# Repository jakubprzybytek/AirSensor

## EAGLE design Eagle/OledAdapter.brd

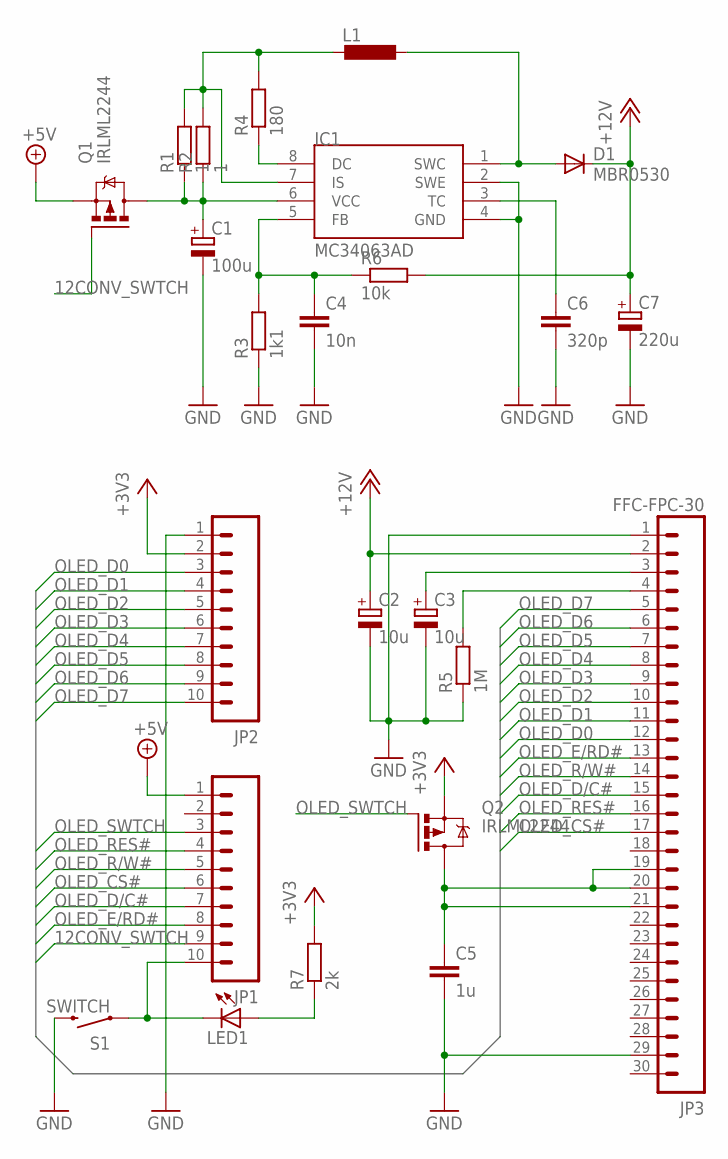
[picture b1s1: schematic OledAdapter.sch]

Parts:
C1: 100u; UD-6,3X7,7_NICHICON
C2, C3: 10u; UD-4X5,8_NICHICON
C4: 10n; C0805
C5: 1u; C1206
C6: 320p; C0805
C7: 220u; UD-6,3X7,7_NICHICON
D1: MBR0530; SOD123
IC1: MC34063AD; SOIC8
JP1, JP2: M10SILK_FEMALE_PTH; 1X10
JP3: FFC-FPC-30; FFC-FPC-30V
L1: L-EUL8530M; L8530M
LED1: LEDSML1206; SML1206
Q1, Q2: IRLML2244; MICRO3
R1, R2: 1; R0805
R3: 1k1; R0805
R4: 180; R0805
R5: 1M; M1206
R6: 10k; R0805
R7: 2k; R0805
S1: SWITCH; TACTILE-SWITCH-1101NE

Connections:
12CONV_SWTCH: JP1.9, Q1.1 (G)
+3V3: JP2.2, Q2.2 (S), R7.2
+5V: JP1.1, Q1.2 (S)
+12V: C2.+, C7.+, D1.C, JP3.2, R6.2
GND: C1.-, C2.-, C3.-, C4.2, C5.2, C6.2, C7.-, IC1.2 (SWE), IC1.4 (GND), JP2.1, JP3.1, JP3.29, R3.1, R5.1, S1.2
unnamed: JP1.10, LED1.C, S1.1
unnamed: LED1.A, R7.1
unnamed: C1.+, IC1.6 (VCC), Q1.3 (D), R1.1, R2.1
unnamed: C3.+, JP3.3
unnamed: C5.1, JP3.19, JP3.20, JP3.21, Q2.3 (D)
unnamed: IC1.7 (IS), L1.2, R1.2, R2.2, R4.2
unnamed: JP3.4, R5.2
unnamed: IC1.8 (DC), R4.1
unnamed: D1.A, IC1.1 (SWC), L1.1
unnamed: C6.1, IC1.3 (TC)
unnamed: C4.1, IC1.5 (FB), R3.2, R6.1
OLED_CS#: JP1.6, JP3.17
OLED_D0: JP2.3, JP3.12
OLED_D1: JP2.4, JP3.11
OLED_D2: JP2.5, JP3.10
OLED_D3: JP2.6, JP3.9
OLED_D4: JP2.7, JP3.8
OLED_D5: JP2.8, JP3.7
OLED_D6: JP2.9, JP3.6
OLED_D7: JP2.10, JP3.5
OLED_D/C#: JP1.7, JP3.15
OLED_E/RD#: JP1.8, JP3.13
OLED_R/W#: JP1.5, JP3.14
OLED_RES#: JP1.4, JP3.16
OLED_SWTCH: JP1.3, Q2.1 (G)

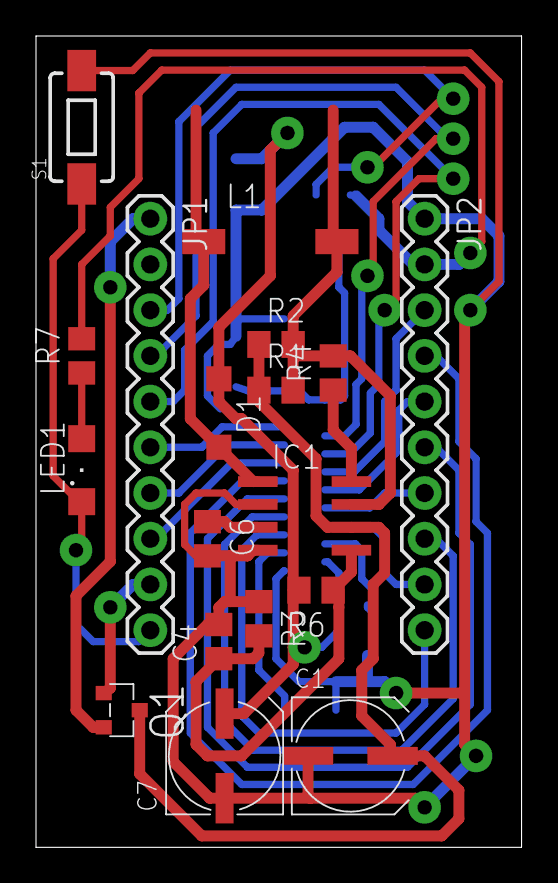
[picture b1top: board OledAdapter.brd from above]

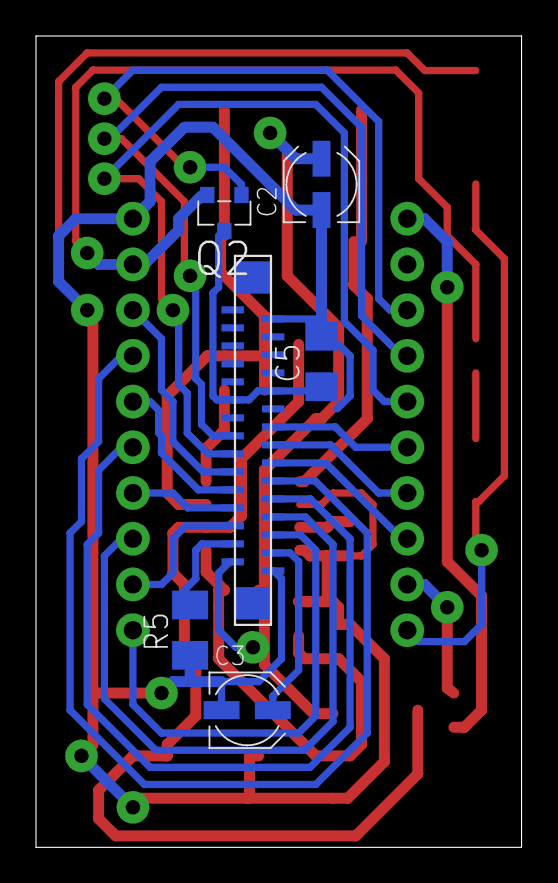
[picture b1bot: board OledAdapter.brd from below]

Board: 2 copper layers, 27.0 x 45.1 mm, 24 parts (6 on the bottom side), 30 nets.

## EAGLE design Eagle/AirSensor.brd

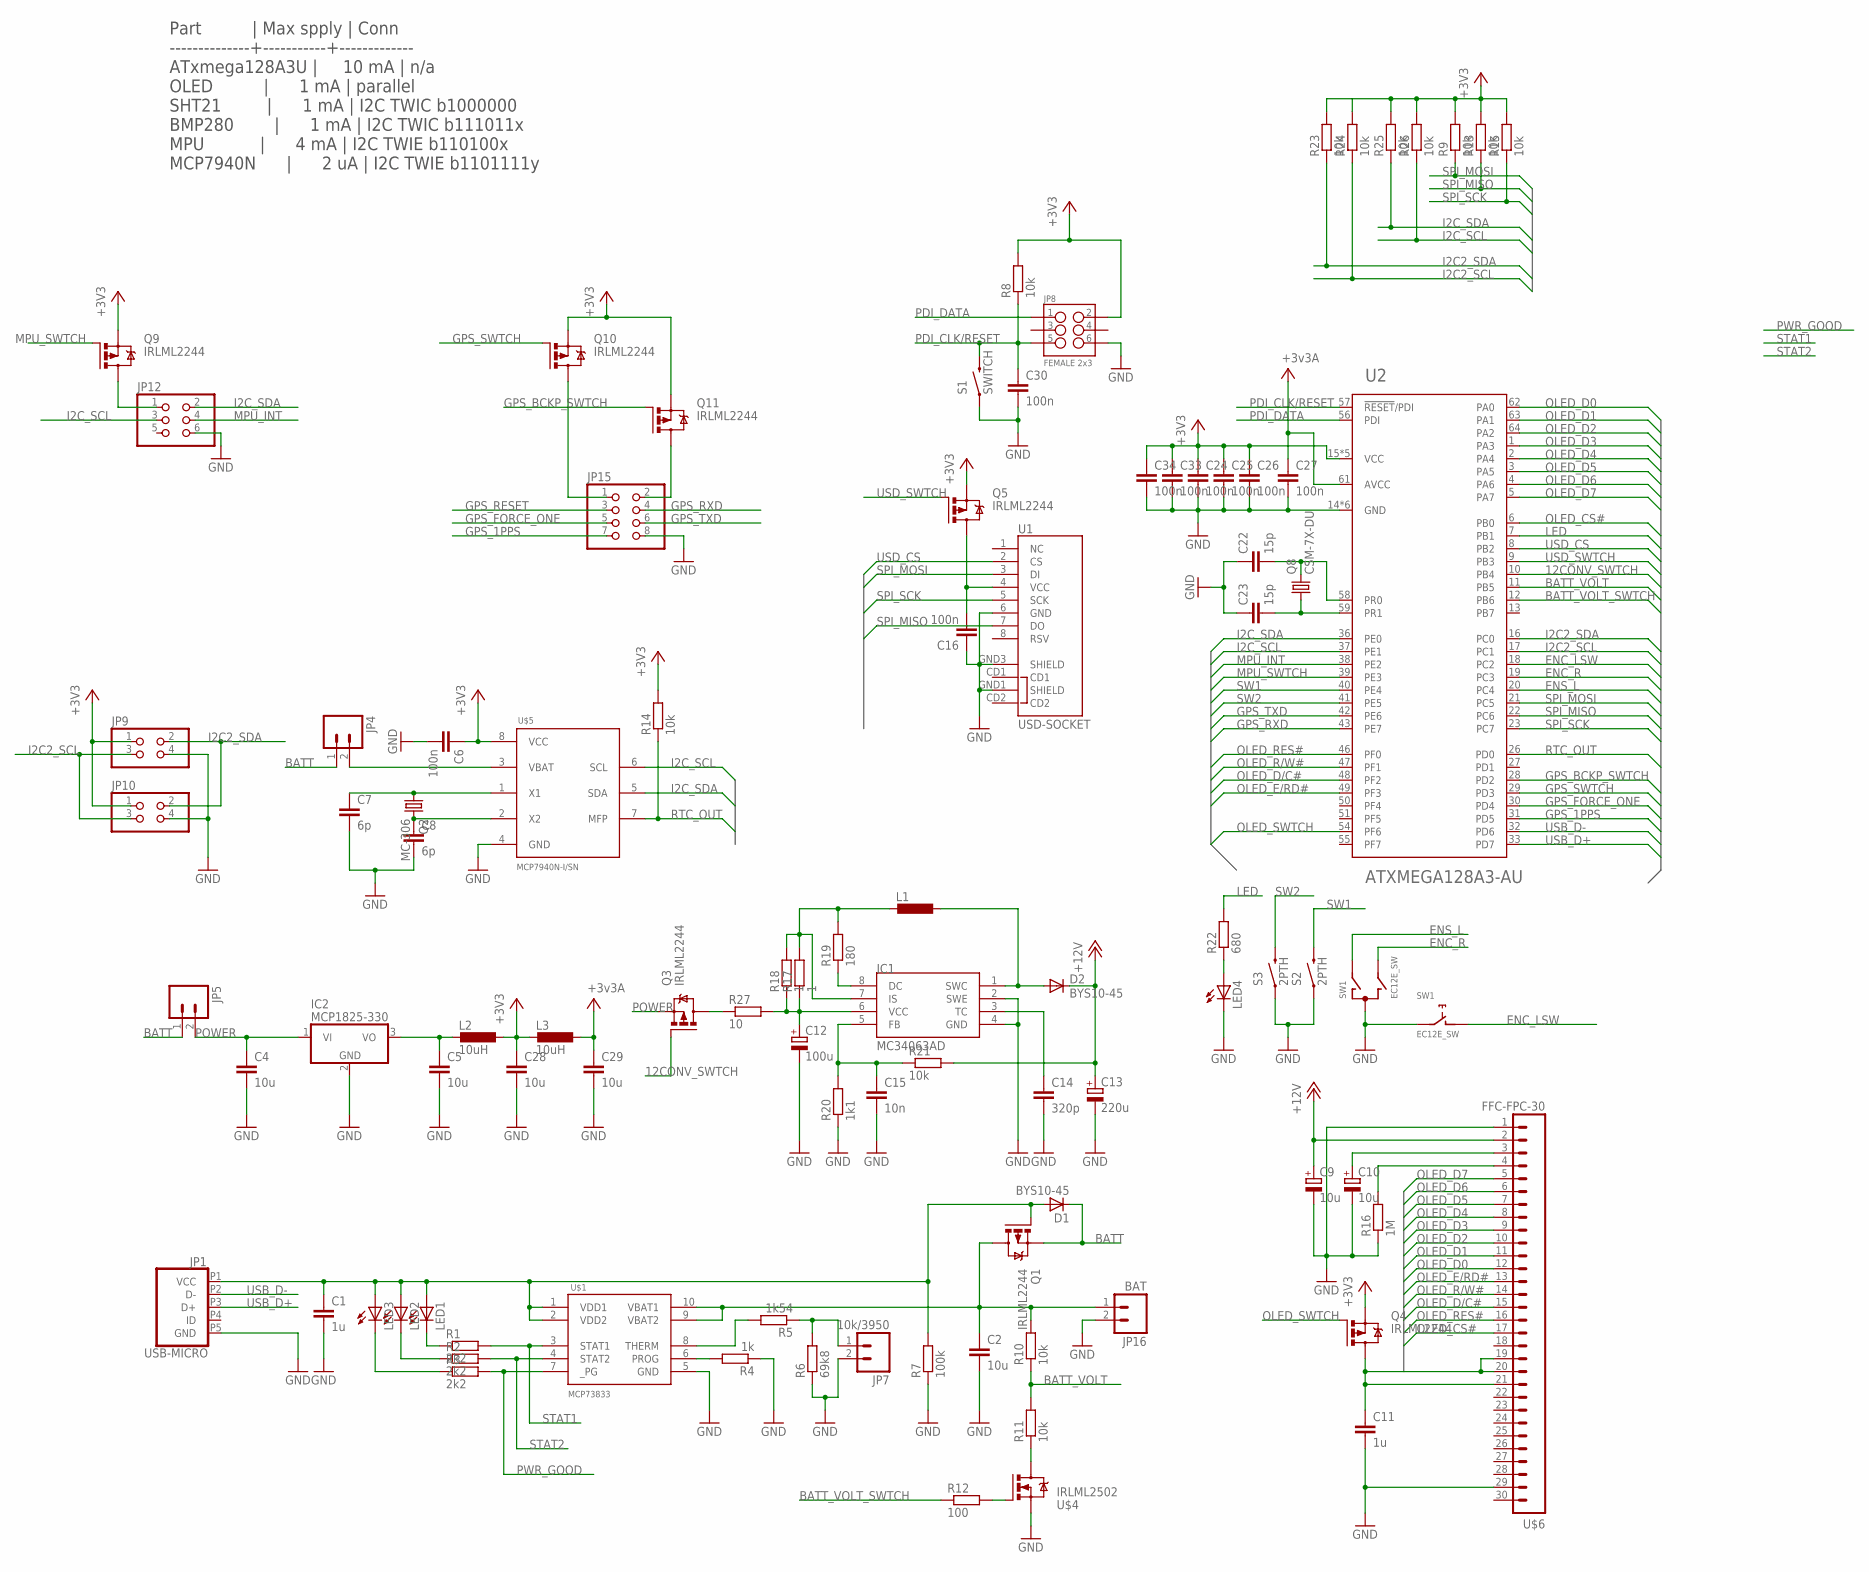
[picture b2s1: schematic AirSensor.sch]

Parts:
C1: 1u; C1206
C2, C4, C5, C28, C29: 10u; C0805
C6, C16, C24, C25, C26, C27, C30, C33, C34: 100n; C0805
C7, C8: 6p; C0805
C9, C10: 10u; UD-4X5,8_NICHICON
C11: 1u; C0805
C12: 100u; SANYO-OSCON_SMD_C6
C13: 220u; SANYO-OSCON_SMD_C6
C14: 320p; C0805
C15: 10n; C0805
C22, C23: 15p; C0805
D1: BYS10-45; SOD106A
D2: BYS10-45; SOD123
IC1: MC34063AD; SOIC8
IC2: MCP1825-330; SOT223
JP1: USB-MICRO; HIROSE-ZX62-AB-5PA(11)
JP4, JP5: M02PTH; 1X02
JP7: 10k/3950; 1X02
JP8: FEMALE 2x3; 2X3
JP9, JP10: PINHD-2X2/90-SOCKET; 2X02S/90
JP12: PINHD-2X3/90-SOCKET; 2X03S/90
JP15: PINHD-2X4/90-SOCKET; 2X04S/90
JP16: BAT; 1X02
L1: L-EUTFI0307; TFI0307
L2, L3: 10uH; L3225P
LED1, LED2, LED3: LEDCHIPLED_1206; CHIPLED_1206
LED4: LEDSML1206; SML1206
Q1, Q3, Q4, Q5, Q9, Q10, Q11: IRLML2244; MICRO3
Q2: MC-306
Q8: CSM-7X-DU
R1, R2, R3: 2k2; R0805
R4: 1k; R0805
R5: 1k54; R0805
R6: 69k8; R0805
R7: 100k; R0805
R8, R9, R10, R11, R13, R14, R15, R21, R23, R24, R25, R26: 10k; R0805
R12: 100; R0805
R16: 1M; R1206
R17, R18: 1; R0805
R19: 180; R0805
R20: 1k1; R0805
R22: 680; R0805
R27: 10; R1206
S1: SWITCH; TACTILE-PTH-SIDEEZ
S2, S3: 2PTH; TACTILE_SWITCH_TALL
SW1: EC12E_SW; ALPS_EC12E_SW
U1: USD-SOCKET; MICROSD_1:1
U2: ATXMEGA128A3-AU; TQFP-64A-64
U$1: MCP73833; MSOP10
U$4: IRLML2502; MICRO3
U$5: MCP7940N-I/SN; SOIC8
U$6: FFC-FPC-30; FFC-FPC-30V

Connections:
12CONV_SWTCH: Q3.1 (G), U2.10 (PB4)
+3V3: C6.1, C24.1, C25.1, C26.1, C28.1, C33.1, C34.1, JP8.2, JP9.1, JP10.1, L2.1, L3.2, Q4.2 (S), Q5.2 (S), Q9.2 (S), Q10.2 (S), Q11.2 (S), R8.2, R9.2, R13.2, R14.2, R15.2, R23.2, R24.2, R25.2, R26.2, U2.15 (VCC), U2.25 (VCC), U2.35 (VCC), U2.45 (VCC), U2.53 (VCC), U$5.8 (VCC)
+12V: C9.+, C13.+, D2.C, R21.2, U$6.2
BATT: D1.K, JP4.1, JP5.1, Q1.2 (S)
BATT_CHARGE: C2.1, JP16.1, Q1.3 (D), R10.2, U$1.9 (VBAT2), U$1.10 (VBAT1)
BATT_VOLT: R10.1, R11.2, U2.11 (PB5)
BATT_VOLT_SWTCH: R12.1, U2.12 (PB6)
ENC_LSW: SW1.D (1), U2.18 (PC2)
ENC_R: SW1.B, U2.19 (PC3)
ENS_L: SW1.A, U2.20 (PC4)
GND: C1.2, C2.2, C4.2, C5.2, C6.2, C7.2, C8.2, C9.-, C10.-, C11.2, C12.-, C13.-, C14.2, C15.2, C16.1, C22.1, C23.1, C24.2, C25.2, C26.2, C27.2, C28.2, C29.2, C30.2, C33.2, C34.2, IC1.2 (SWE), IC1.4 (GND), IC2.2 (GND), JP1.P5 (GND), JP7.2, JP8.6, JP9.4, JP10.4, JP12.6, JP15.8, JP16.2, LED4.C, R4.1, R6.1, R7.1, R16.1, R20.1, S1.1, S2.A2 (1), S3.A2 (1), SW1.C, SW1.E (2), U1.6 (GND), U1.GND1 (SHIELD), U1.GND3 (SHIELD), U2.14 (GND), U2.24 (GND), U2.34 (GND), U2.44 (GND), U2.52 (GND), U2.60 (GND), U$1.5 (GND), U$4.2 (S), U$5.4 (GND), U$6.1, U$6.29
GPS_1PPS: JP15.7, U2.31 (PD5)
GPS_BCKP_SWTCH: Q11.1 (G), U2.28 (PD2)
GPS_FORCE_ONE: JP15.5, U2.30 (PD4)
GPS_RESET: JP15.3
GPS_RXD: JP15.4, U2.43 (PE7)
GPS_SWTCH: Q10.1 (G), U2.29 (PD3)
GPS_TXD: JP15.6, U2.42 (PE6)
I2C2_SCL: JP9.3, JP10.3, R24.1, U2.17 (PC1)
I2C2_SDA: JP9.2, JP10.2, R23.1, U2.16 (PC0)
I2C_SCL: JP12.3, R26.1, U2.37 (PE1), U$5.6 (SCL)
I2C_SDA: JP12.2, R25.1, U2.36 (PE0), U$5.5 (SDA)
LED: R22.2, U2.7 (PB1)
MPU_INT: JP12.4, U2.38 (PE2)
MPU_SWTCH: Q9.1 (G), U2.39 (PE3)
unnamed: LED1.C, R1.1
unnamed: C1.1, D1.A, JP1.P1 (VCC), LED1.A, LED2.A, LED3.A, Q1.1 (G), R7.2, U$1.1 (VDD1), U$1.2 (VDD2)
unnamed: C7.1, Q2.1, U$5.1 (X1)
unnamed: C8.1, Q2.4 (2), U$5.2 (X2)
unnamed: JP4.2, U$5.3 (VBAT)
unnamed: LED2.C, R2.1
unnamed: LED3.C, R3.1
unnamed: R4.2, U$1.6 (PROG)
unnamed: R12.2, U$4.1 (G)
unnamed: R5.2, U$1.8 (THERM)
unnamed: JP7.1, R5.1, R6.2
unnamed: Q3.3 (D), R27.1
unnamed: R11.1, U$4.3 (D)
unnamed: C12.+, IC1.6 (VCC), R17.1, R18.1, R27.2
unnamed: C10.+, U$6.3
unnamed: C11.1, Q4.3 (D), U$6.19, U$6.20, U$6.21
unnamed: IC1.7 (IS), L1.2, R17.2, R18.2, R19.2
unnamed: R16.2, U$6.4
unnamed: IC1.8 (DC), R19.1
unnamed: D2.A, IC1.1 (SWC), L1.1
unnamed: C14.1, IC1.3 (TC)
unnamed: C15.1, IC1.5 (FB), R20.2, R21.1
unnamed: C16.2, Q5.3 (D), U1.4 (VCC)
unnamed: C22.2, Q8.2, U2.58 (PR0)
unnamed: C23.2, Q8.1, U2.59 (PR1)
unnamed: C5.1, IC2.3 (VO), L2.2
unnamed: LED4.A, R22.1
unnamed: JP12.1, Q9.3 (D)
unnamed: JP15.1, Q10.3 (D)
unnamed: JP15.2, Q11.3 (D)
OLED_CS#: U2.6 (PB0), U$6.17
OLED_D0: U2.62 (PA0), U$6.12
OLED_D1: U2.63 (PA1), U$6.11
OLED_D2: U2.64 (PA2), U$6.10
OLED_D3: U2.1 (PA3), U$6.9
OLED_D4: U2.2 (PA4), U$6.8
OLED_D5: U2.3 (PA5), U$6.7
OLED_D6: U2.4 (PA6), U$6.6
OLED_D7: U2.5 (PA7), U$6.5
OLED_D/C#: U2.48 (PF2), U$6.15
OLED_E/RD#: U2.49 (PF3), U$6.13
OLED_R/W#: U2.47 (PF1), U$6.14
OLED_RES#: U2.46 (PF0), U$6.16
OLED_SWTCH: Q4.1 (G), U2.54 (PF6)
PDI_CLK/RESET: C30.1, JP8.5, R8.1, S1.2, U2.57 (!RESET!/PDI)
PDI_DATA: JP8.1, U2.56 (PDI)
POWER: C4.1, IC2.1 (VI), JP5.2, Q3.2 (S)
PWR_GOOD: R3.2, U$1.7 (_PG)
RTC_OUT: R14.1, U2.26 (PD0), U$5.7 (MFP)
SPI_MISO: R13.1, U1.7 (DO), U2.22 (PC6)
SPI_MOSI: R9.1, U1.3 (DI), U2.21 (PC5)
SPI_SCK: R15.1, U1.5 (SCK), U2.23 (PC7)
STAT1: R1.2, U$1.3 (STAT1)
STAT2: R2.2, U$1.4 (STAT2)
SW1: S2.B2 (2), U2.40 (PE4)
SW2: S3.B2 (2), U2.41 (PE5)
USB_D+: JP1.P3 (D+), U2.33 (PD7)
USB_D-: JP1.P2 (D-), U2.32 (PD6)
USD_CS: U1.2 (CS), U2.8 (PB2)
USD_SWTCH: Q5.1 (G), U2.9 (PB3)
V+: C27.1, C29.1, L3.1, U2.61 (AVCC)

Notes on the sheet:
Part | Max spply | Conn --------------+-----------+------------- ATxmega128A3U | 10 mA | n/a OLED | 1 mA | parallel SHT21 | 1 mA | I2C TWIC b1000000 BMP280 | 1 mA | I2C TWIC b111011x MPU | 4 mA | I2C TWIE b110100x MCP7940N | 2 uA | I2C TWIE b1101111y

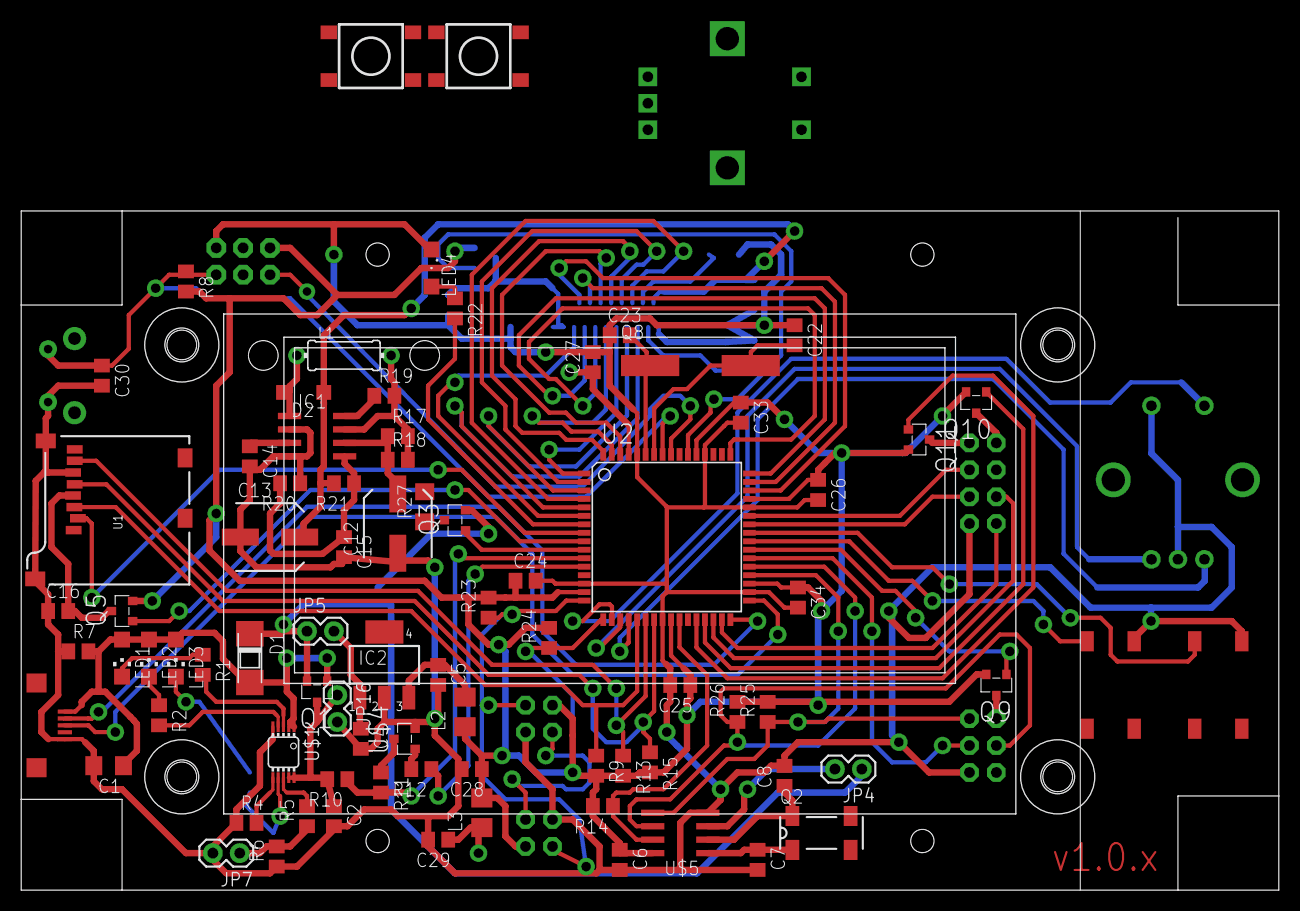
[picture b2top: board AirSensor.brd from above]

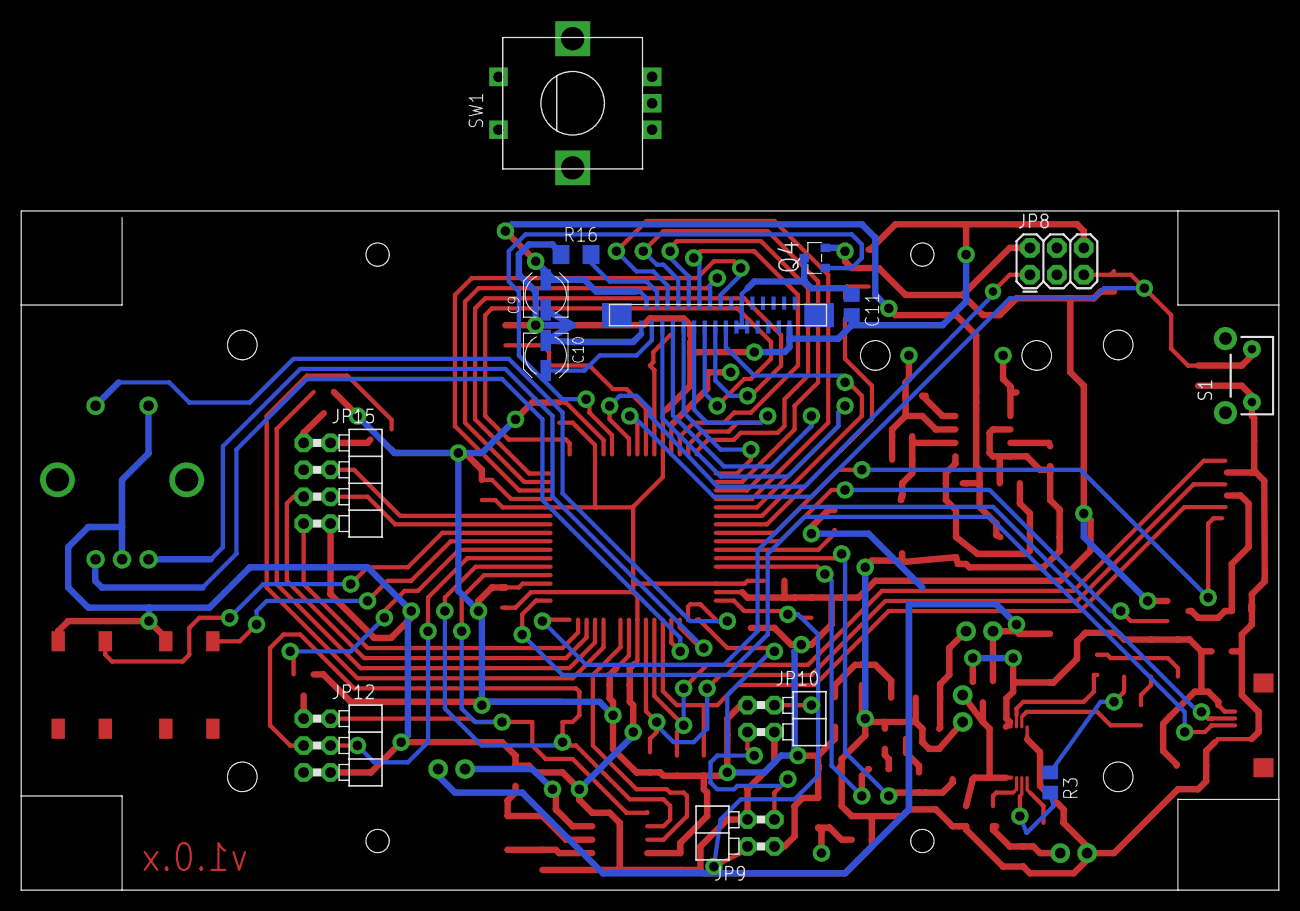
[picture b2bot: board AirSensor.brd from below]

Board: 2 copper layers, 118.7 x 64.1 mm, 94 parts (15 on the bottom side), 85 nets.

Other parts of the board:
U$7: RET012864LYPP3N

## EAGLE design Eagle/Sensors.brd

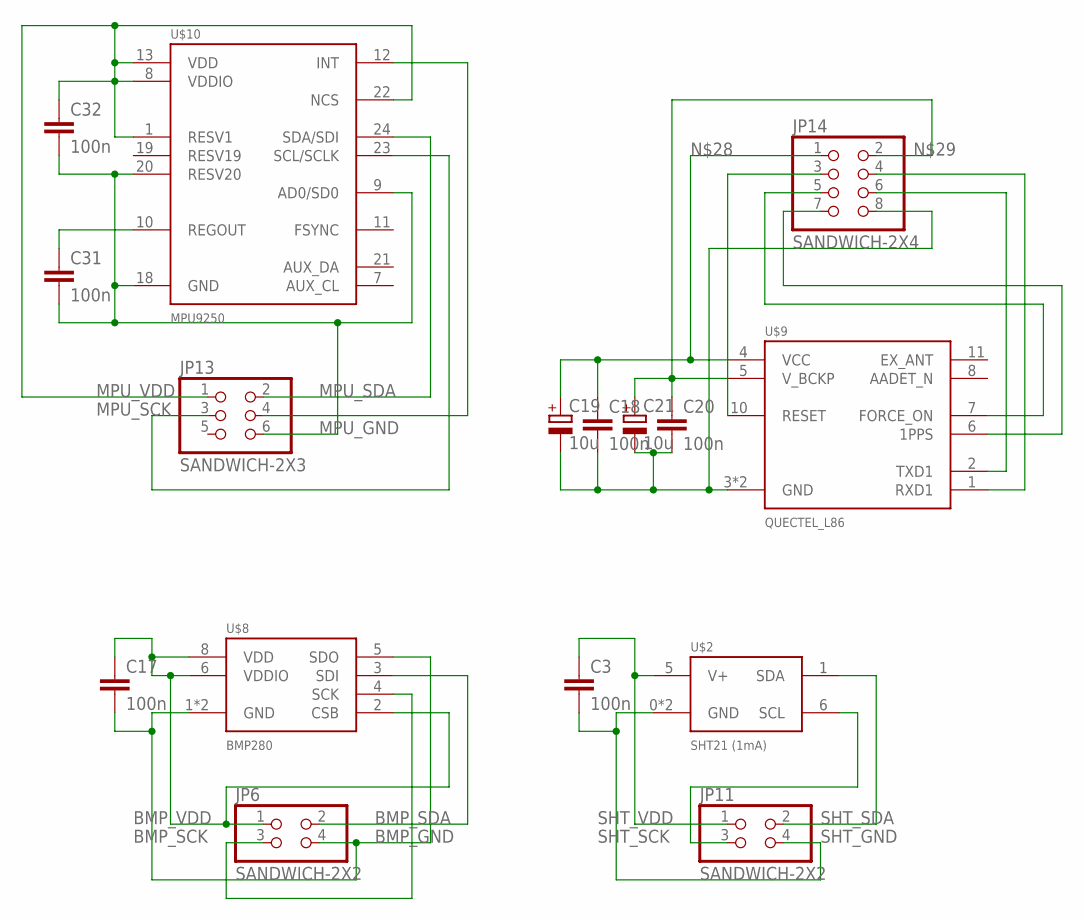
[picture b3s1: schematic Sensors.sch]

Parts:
C3, C17, C18, C20, C31, C32: 100n; C0805
C19, C21: 10u; UD-4X5,8_NICHICON
JP6, JP11: SANDWICH-2X2
JP13: SANDWICH-2X3
JP14: SANDWICH-2X4
U$2: SHT21 (1mA); DFN6
U$8: BMP280
U$9: QUECTEL_L86
U$10: MPU9250; QFN-24

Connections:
BMP_GND: C17.2, JP6.4, U$8.1 (GND), U$8.5 (SDO), U$8.7 (GND)
BMP_SCK: JP6.3, U$8.4 (SCK)
BMP_SDA: JP6.2, U$8.3 (SDI)
BMP_VDD: C17.1, JP6.1, U$8.2 (CSB), U$8.6 (VDDIO), U$8.8 (VDD)
MPU_GND: C31.2, C32.2, JP13.6, U$10.9 (AD0/SD0), U$10.18 (GND), U$10.20 (RESV20)
MPU_SCK: JP13.3, U$10.23 (SCL/SCLK)
MPU_SDA: JP13.2, U$10.24 (SDA/SDI)
MPU_VDD: C32.1, JP13.1, U$10.1 (RESV1), U$10.8 (VDDIO), U$10.13 (VDD), U$10.22 (NCS)
unnamed: C18.1, C19.+, JP14.1, U$9.4 (VCC)
unnamed: C20.1, C21.+, JP14.2, U$9.5 (V_BCKP)
unnamed: C31.1, U$10.10 (REGOUT)
unnamed: JP13.4, U$10.12 (INT)
unnamed: JP14.3, U$9.10 (RESET)
unnamed: JP14.6, U$9.2 (TXD1)
unnamed: JP14.4, U$9.1 (RXD1)
unnamed: JP14.5, U$9.7 (FORCE_ON)
unnamed: JP14.7, U$9.6 (1PPS)
unnamed: C18.2, C19.-, C20.2, C21.-, JP14.8, U$9.3 (GND), U$9.12 (GND)
SHT_GND: C3.2, JP11.4, U$2.0 (GND), U$2.2 (GND)
SHT_SCK: JP11.3, U$2.6 (SCL)
SHT_SDA: JP11.2, U$2.1 (SDA)
SHT_VDD: C3.1, JP11.1, U$2.5 (V+)

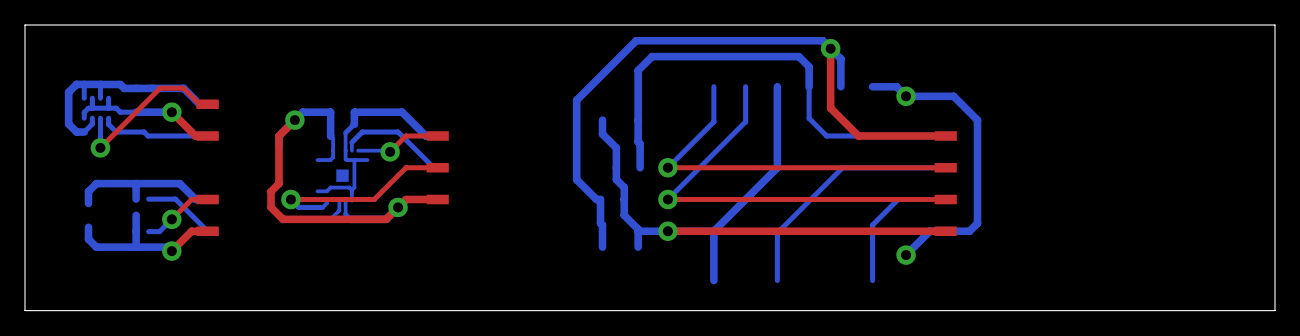
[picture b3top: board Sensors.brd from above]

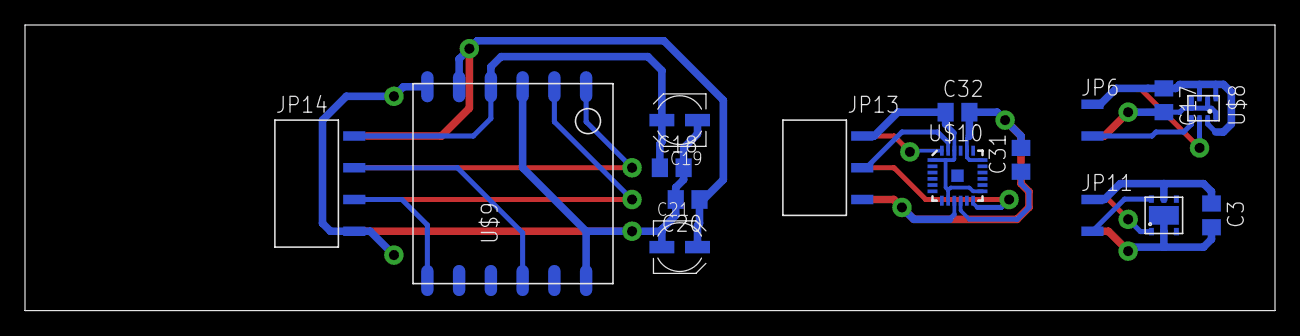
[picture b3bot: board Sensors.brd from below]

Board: 2 copper layers, 100.0 x 22.9 mm, 16 parts (16 on the bottom side), 22 nets.

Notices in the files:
parts and their libraries:
SparkFun-Connectors: Licensing: Creative Commons ShareAlike 4.0 International - https://creativecommons.org/licenses/by-sa/4.0
